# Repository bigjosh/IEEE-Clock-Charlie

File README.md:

# IEEE-Clock-Chalie
 
Clock for IEEE Spectrum magazine. 

Looks a little something like this...

https://www.youtube.com/watch?v=FqGKZdCMA6w

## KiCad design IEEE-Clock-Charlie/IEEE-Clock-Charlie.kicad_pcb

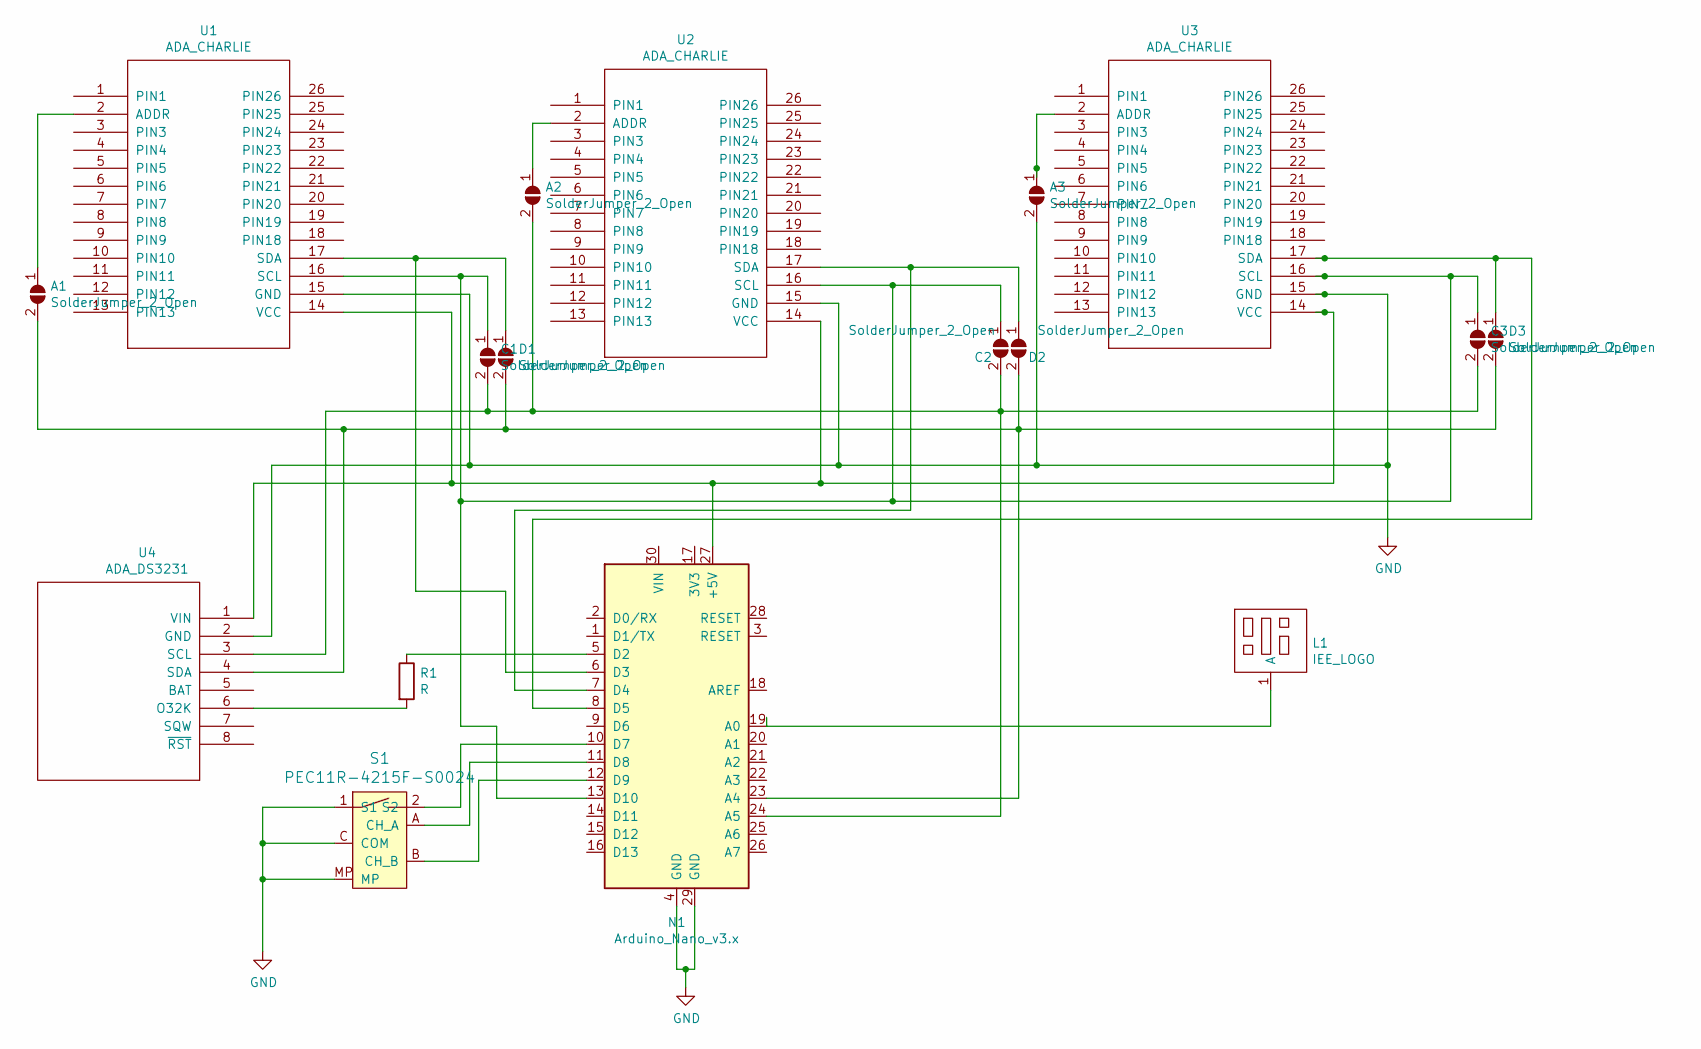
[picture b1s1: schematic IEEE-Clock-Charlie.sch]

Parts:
A1, A2, A3: SolderJumper_2_Open; SolderJumper-2_P1.3mm_Open_RoundedPad1.0x1.5mm
C1, C2, C3: SolderJumper_2_Open; SolderJumper-2_P1.3mm_Open_RoundedPad1.0x1.5mm
D1, D2, D3: SolderJumper_2_Open; SolderJumper-2_P1.3mm_Open_RoundedPad1.0x1.5mm
L1: IEE_LOGO; IEEE_LOGO
N1: Arduino_Nano_v3.x; Arduino_Nano
R1: R; R_0603_1608Metric
S1: PEC11R-4215F-S0024; RotaryEncoder_Alps_EC11E_Vertical_H20mm; MPN PEC11R-4215F-S0024; Digi-Key_PN PEC11R-4215F-S0024-ND
U1, U2, U3: ADA_CHARLIE; DIP-26_1000_ELL
U4: ADA_DS3231; PinHeader_1x08_P2.54mm_Vertical

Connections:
GND: A3.2 (B), N1.4 (GND), N1.29 (GND), S1.1 (S1), S1.C (COM), S1.MP, U1.15 (GND), U2.15 (GND), U3.15 (GND), U4.2 (GND)
unnamed: A1.1 (A), U1.2 (ADDR)
unnamed: A1.2 (B), D1.2 (B), D2.2 (B), D3.2 (B), N1.23 (A4), U4.4 (SDA)
unnamed: A2.1 (A), U2.2 (ADDR)
unnamed: A2.2 (B), C1.2 (B), C2.2 (B), C3.2 (B), N1.24 (A5), U4.3 (SCL)
unnamed: A3.1 (A), U3.2 (ADDR)
unnamed: C1.1 (A), C2.1 (A), C3.1 (A), N1.13 (D10), U1.16 (SCL), U2.16 (SCL), U3.16 (SCL)
unnamed: D1.1 (A), N1.6 (D3), U1.17 (SDA)
unnamed: D2.1 (A), N1.7 (D4), U2.17 (SDA)
unnamed: D3.1 (A), N1.8 (D5), U3.17 (SDA)
unnamed: L1.1, N1.19 (A0)
unnamed: N1.5 (D2), R1.1
unnamed: N1.10 (D7), S1.2 (S2)
unnamed: N1.11 (D8), S1.A (CH_A)
unnamed: N1.12 (D9), S1.B (CH_B)
unnamed: N1.27 (+5V), U1.14 (VCC), U2.14 (VCC), U3.14 (VCC), U4.1 (VIN)
unnamed: R1.2, U4.6 (O32K)

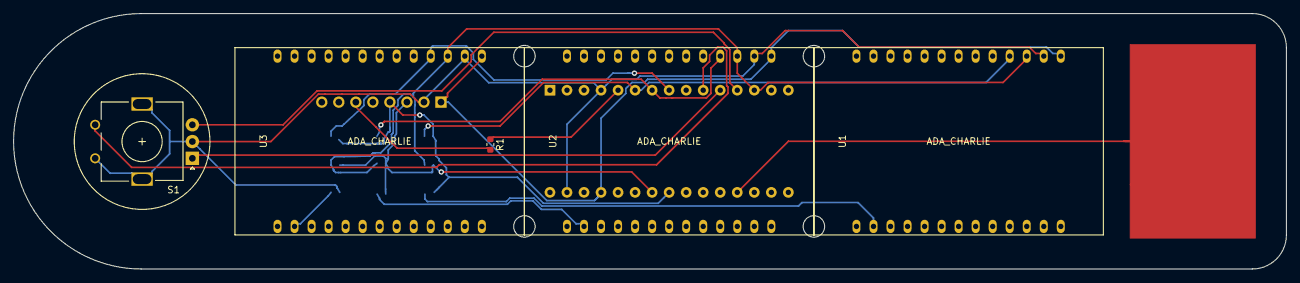
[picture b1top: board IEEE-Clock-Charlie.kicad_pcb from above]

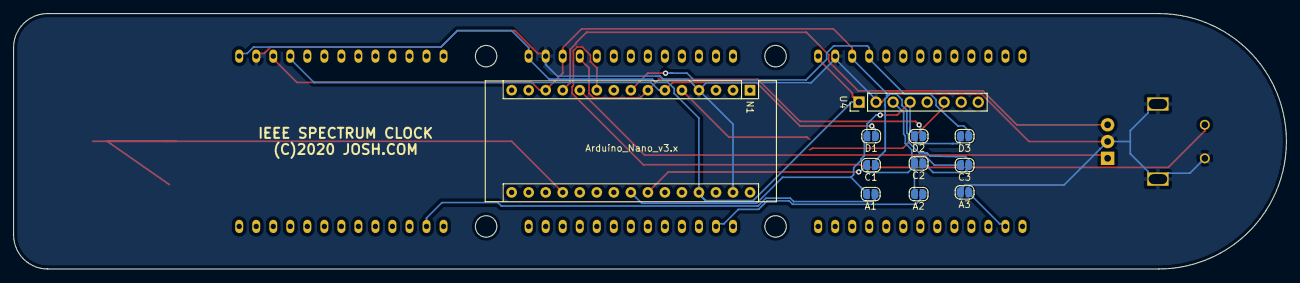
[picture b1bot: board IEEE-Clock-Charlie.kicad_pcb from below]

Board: 2 copper layers, 189.9 x 38.1 mm, 21 parts (11 on the bottom side), 17 nets.

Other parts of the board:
M1, M2, M3, M4: MountingHole_3.2mm_M3

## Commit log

2020-01-19 Iniital commint
    Charlie display symbol created, schematic started
2020-01-20 add lib back in from gitignire
2020-01-30 First rev ordered OSHPARK
2020-02-09 Add jumpers for CLK and DAT
    Make it so displays can be individually driven rather than shared TWI
2020-02-10 With jumpers routed and ready to go
2020-02-10 Layout clean up traces
2020-02-16 ALLPCB produced output files
2020-02-16 Working 3 way demo
2020-02-16 Initial demo done

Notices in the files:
IEEE-Clock-Charlie/IEEE-Clock-Charlie.kicad_pcb:
(C)2020 JOSH.COM
